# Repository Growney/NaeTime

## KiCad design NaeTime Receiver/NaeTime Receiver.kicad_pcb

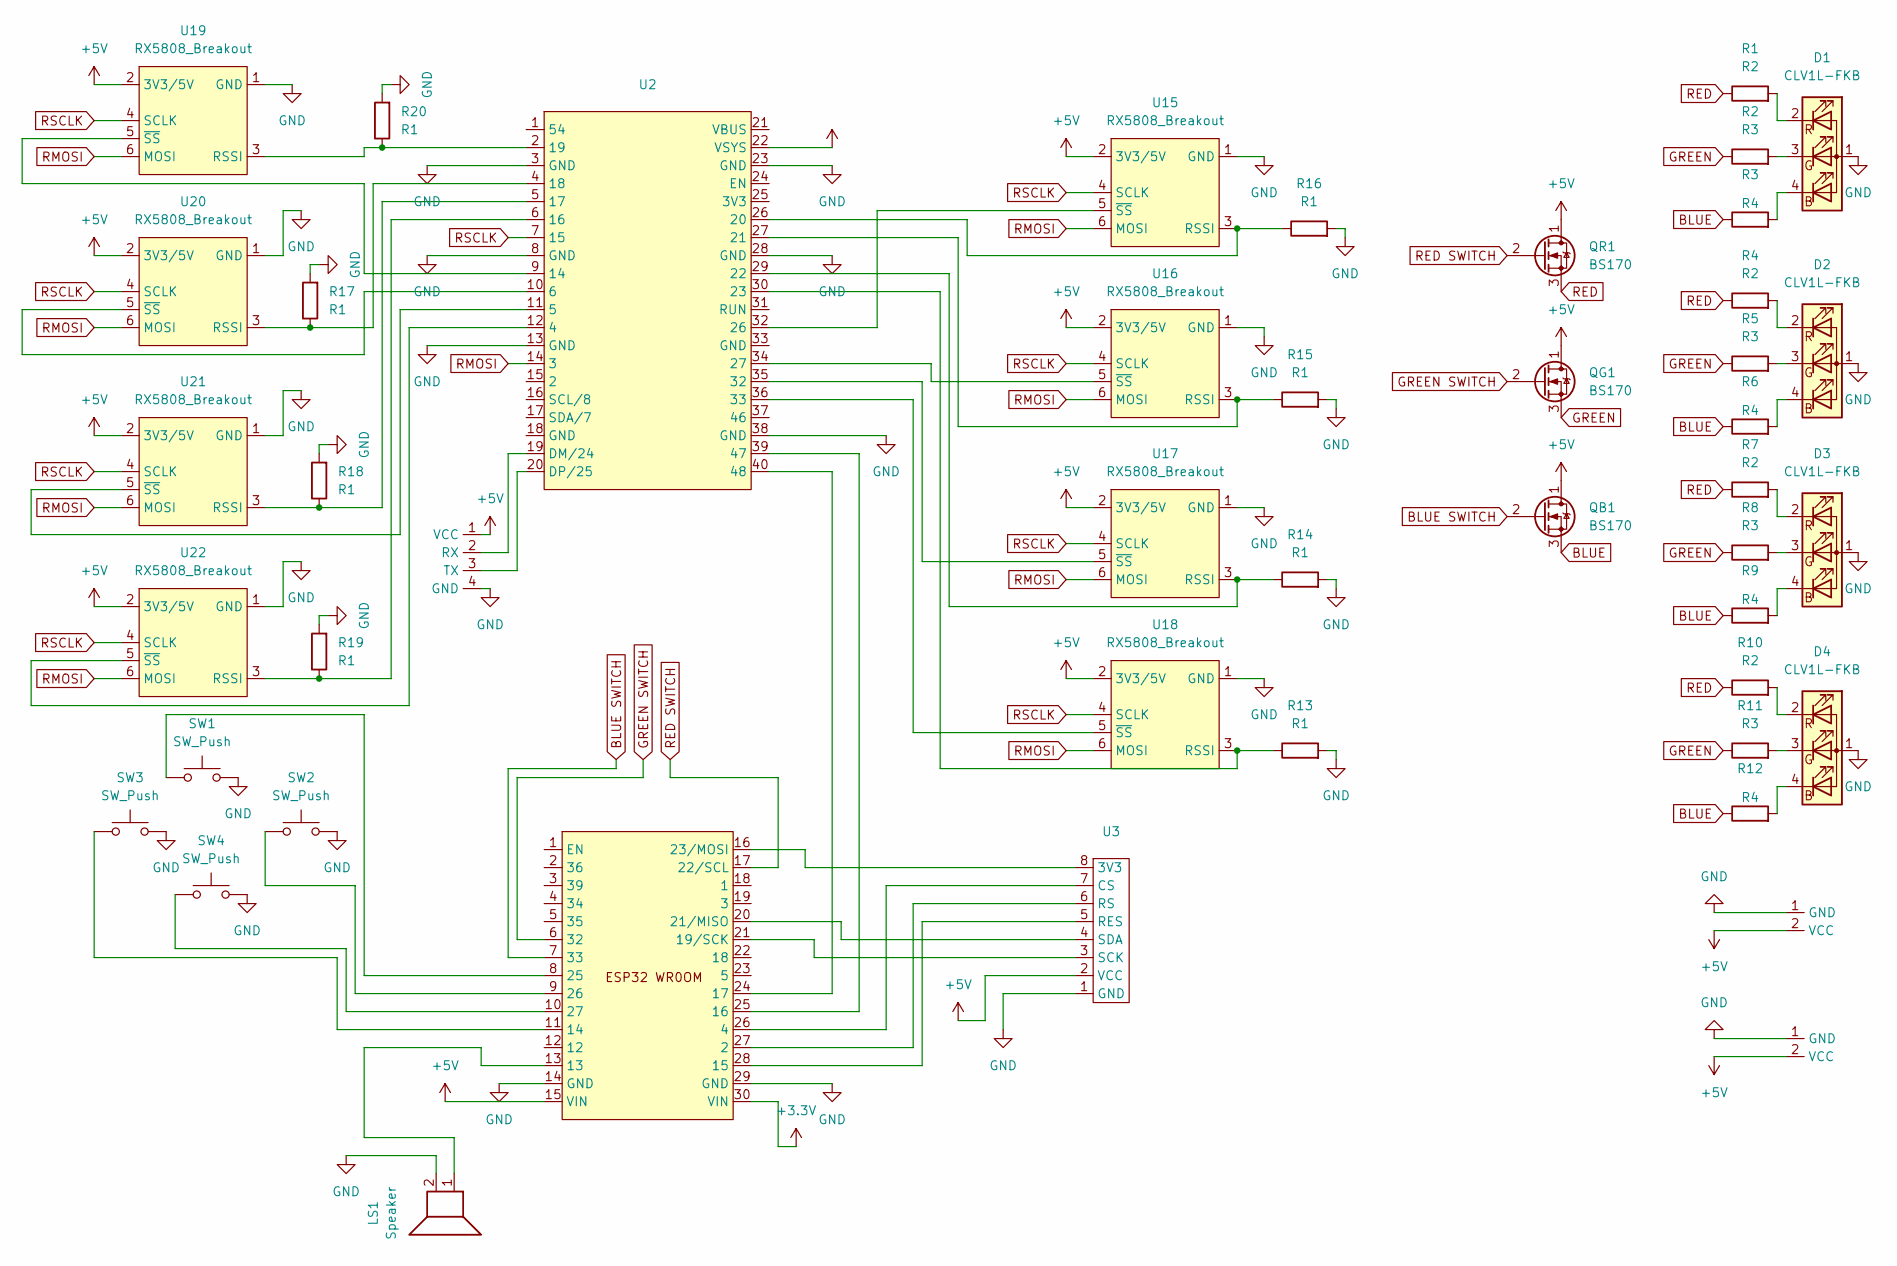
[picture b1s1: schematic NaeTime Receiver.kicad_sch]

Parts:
D1, D2, D3, D4: CLV1L-FKB; LED_D5.0mm-4_RGB GBCR
LS1: Speaker; Buzzer_12x9.5RM7.6
QB1: BS170; TO-92_Inline
QG1: BS170; TO-92_Inline
QR1: BS170; TO-92_Inline
R1, R4, R7, R10: R2; R_Axial_DIN0204_L3.6mm_D1.6mm_P7.62mm_Horizontal
R2, R5, R8, R11: R3; R_Axial_DIN0204_L3.6mm_D1.6mm_P7.62mm_Horizontal
R3, R6, R9, R12: R4; R_Axial_DIN0204_L3.6mm_D1.6mm_P7.62mm_Horizontal
R13, R14, R15, R16, R17, R18, R19, R20: R1; R_Axial_DIN0204_L3.6mm_D1.6mm_P7.62mm_Horizontal
SW1, SW2, SW3, SW4: SW_Push; SW_PUSH_6mm_H5mm
U1: ESP32 WROOM 30Pin Dev Board
U2: Wavestore ESP32-P4-ETH
U3: ST7735 Pin Header
U4: Exposed UART
U7, U8: Power Pads
U15, U16, U17, U18, U19, U20, U21, U22: RX5808_Breakout

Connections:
+3.3V: U1.30 (VIN)
+5V: QB1.1 (D), QG1.1 (D), QR1.1 (D), U1.15 (VIN), U2.22 (VSYS), U3.2 (VCC), U4.1 (VCC), U7.2 (VCC), U8.2 (VCC), U15.2 (3V3/5V), U16.2 (3V3/5V), U17.2 (3V3/5V), U18.2 (3V3/5V), U19.2 (3V3/5V), U20.2 (3V3/5V), U21.2 (3V3/5V), U22.2 (3V3/5V)
BLUE: QB1.3 (S), R3.1, R6.1, R9.1, R12.1
BLUE SWITCH: QB1.2 (G), U1.7 (33)
GND: D1.1 (A), D2.1 (A), D3.1 (A), D4.1 (A), LS1.2, R13.2, R14.2, R15.2, R16.2, R17.2, R18.2, R19.2, R20.2, SW1.2, SW2.2, SW3.2, SW4.2, U1.14 (GND), U1.29 (GND), U2.3 (GND), U2.8 (GND), U2.13 (GND), U2.23 (GND), U2.28 (GND), U2.38 (GND), U3.1 (GND), U4.4 (GND), U7.1 (GND), U8.1 (GND), U15.1 (GND), U16.1 (GND), U17.1 (GND), U18.1 (GND), U19.1 (GND), U20.1 (GND), U21.1 (GND), U22.1 (GND)
GREEN: QG1.3 (S), R2.1, R5.1, R8.1, R11.1
GREEN SWITCH: QG1.2 (G), U1.6 (32)
unnamed: D1.4 (BK), R3.2
unnamed: D1.3 (GK), R2.2
unnamed: D1.2 (RK), R1.2
unnamed: D2.4 (BK), R6.2
unnamed: D2.3 (GK), R5.2
unnamed: D2.2 (RK), R4.2
unnamed: D3.4 (BK), R9.2
unnamed: D3.3 (GK), R8.2
unnamed: D3.2 (RK), R7.2
unnamed: D4.4 (BK), R12.2
unnamed: D4.3 (GK), R11.2
unnamed: D4.2 (RK), R10.2
unnamed: LS1.1, U1.13
unnamed: U1.27 (2), U3.6 (RS)
unnamed: U1.26 (4), U3.7 (CS)
unnamed: SW3.1, U1.11 (14)
unnamed: U1.28 (15), U3.5 (RES)
unnamed: U1.25 (16), U2.39 (47)
unnamed: U1.24 (17), U2.40 (48)
unnamed: U1.21 (19/SCK), U3.3 (SCK)
unnamed: U1.20 (21/MISO), U3.4 (SDA)
unnamed: U1.16 (23/MOSI), U3.8 (3V3)
unnamed: SW1.1, U1.8 (25)
unnamed: SW2.1, U1.9 (26)
unnamed: SW4.1, U1.10 (27)
unnamed: U2.12 (4), U22.5 (~SS)
unnamed: U2.11 (5), U21.5 (~SS)
unnamed: U2.10 (6), U20.5 (~SS)
unnamed: R19.1, U2.6 (16), U22.3 (RSSI)
unnamed: R18.1, U2.5 (17), U21.3 (RSSI)
unnamed: R17.1, U2.4 (18), U20.3 (RSSI)
unnamed: U2.19 (DM/24), U4.2 (RX)
unnamed: U2.20 (DP/25), U4.3 (TX)
unnamed: R16.1, U2.26 (20), U15.3 (RSSI)
unnamed: U2.32 (26), U15.5 (~SS)
unnamed: R15.1, U2.27 (21), U16.3 (RSSI)
unnamed: U2.34 (27), U16.5 (~SS)
unnamed: R14.1, U2.29 (22), U17.3 (RSSI)
unnamed: U2.35 (32), U17.5 (~SS)
unnamed: R13.1, U2.30 (23), U18.3 (RSSI)
unnamed: U2.36 (33), U18.5 (~SS)
unnamed: R20.1, U2.2 (19), U19.3 (RSSI)
unnamed: U2.9 (14), U19.5 (~SS)
RED: QR1.3 (S), R1.1, R4.1, R7.1, R10.1
RED SWITCH: QR1.2 (G), U1.17 (22/SCL)
RMOSI: U2.14 (3), U15.6 (MOSI), U16.6 (MOSI), U17.6 (MOSI), U18.6 (MOSI), U19.6 (MOSI), U20.6 (MOSI), U21.6 (MOSI), U22.6 (MOSI)
RSCLK: U2.7 (15), U15.4 (SCLK), U16.4 (SCLK), U17.4 (SCLK), U18.4 (SCLK), U19.4 (SCLK), U20.4 (SCLK), U21.4 (SCLK), U22.4 (SCLK)

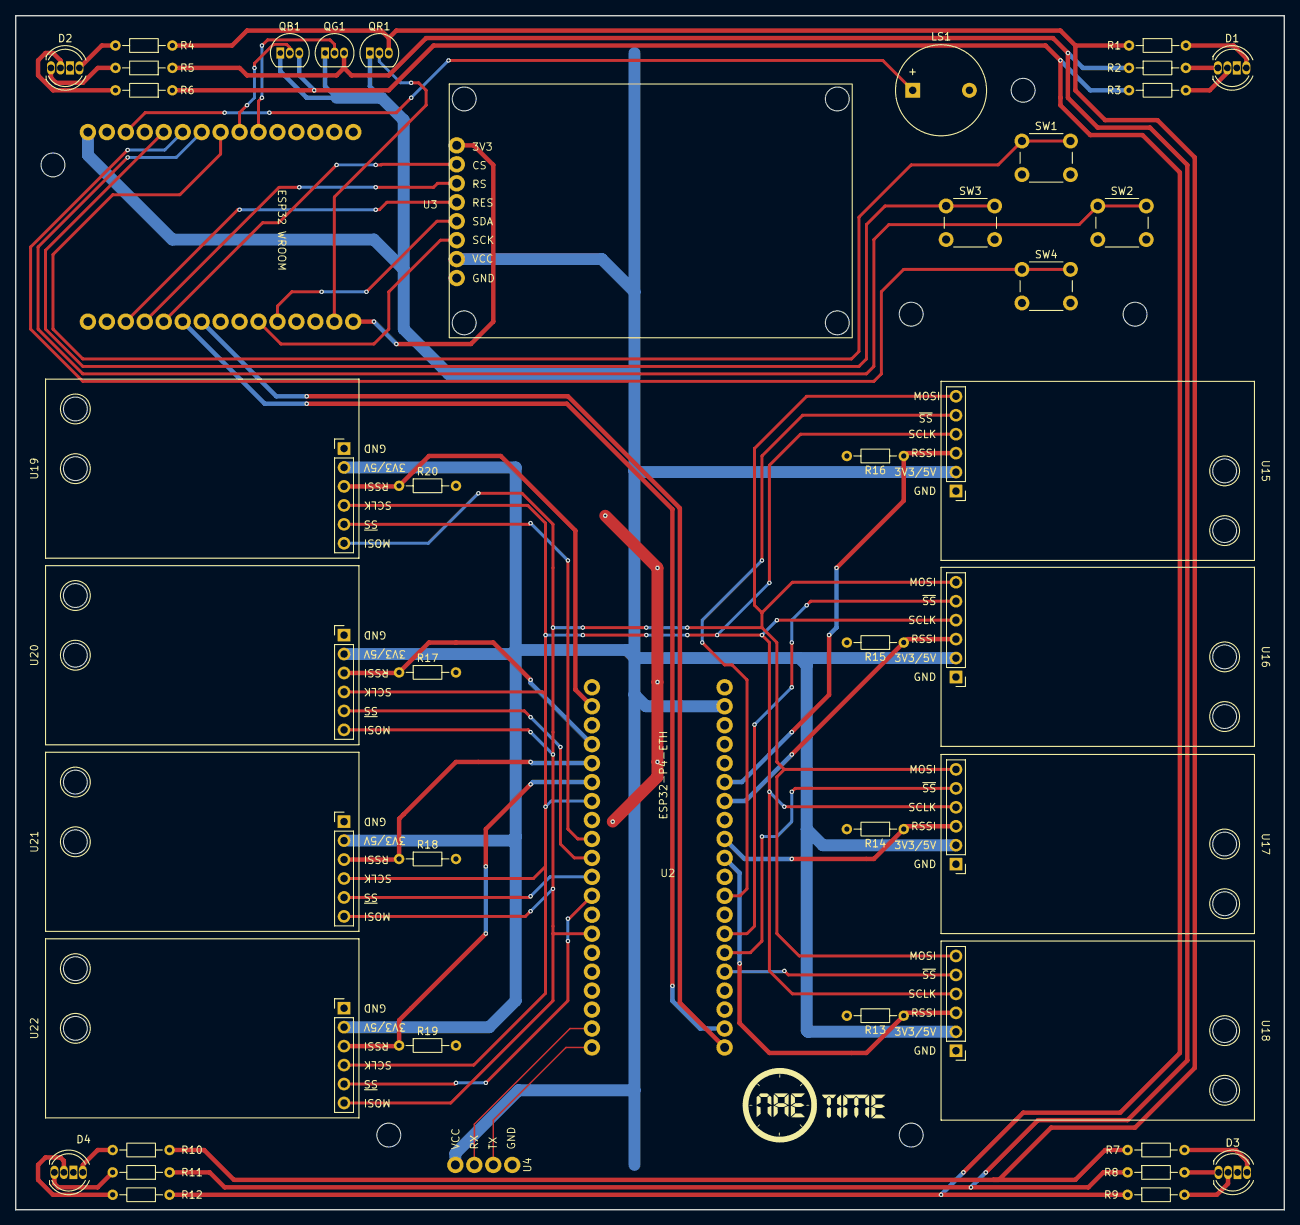
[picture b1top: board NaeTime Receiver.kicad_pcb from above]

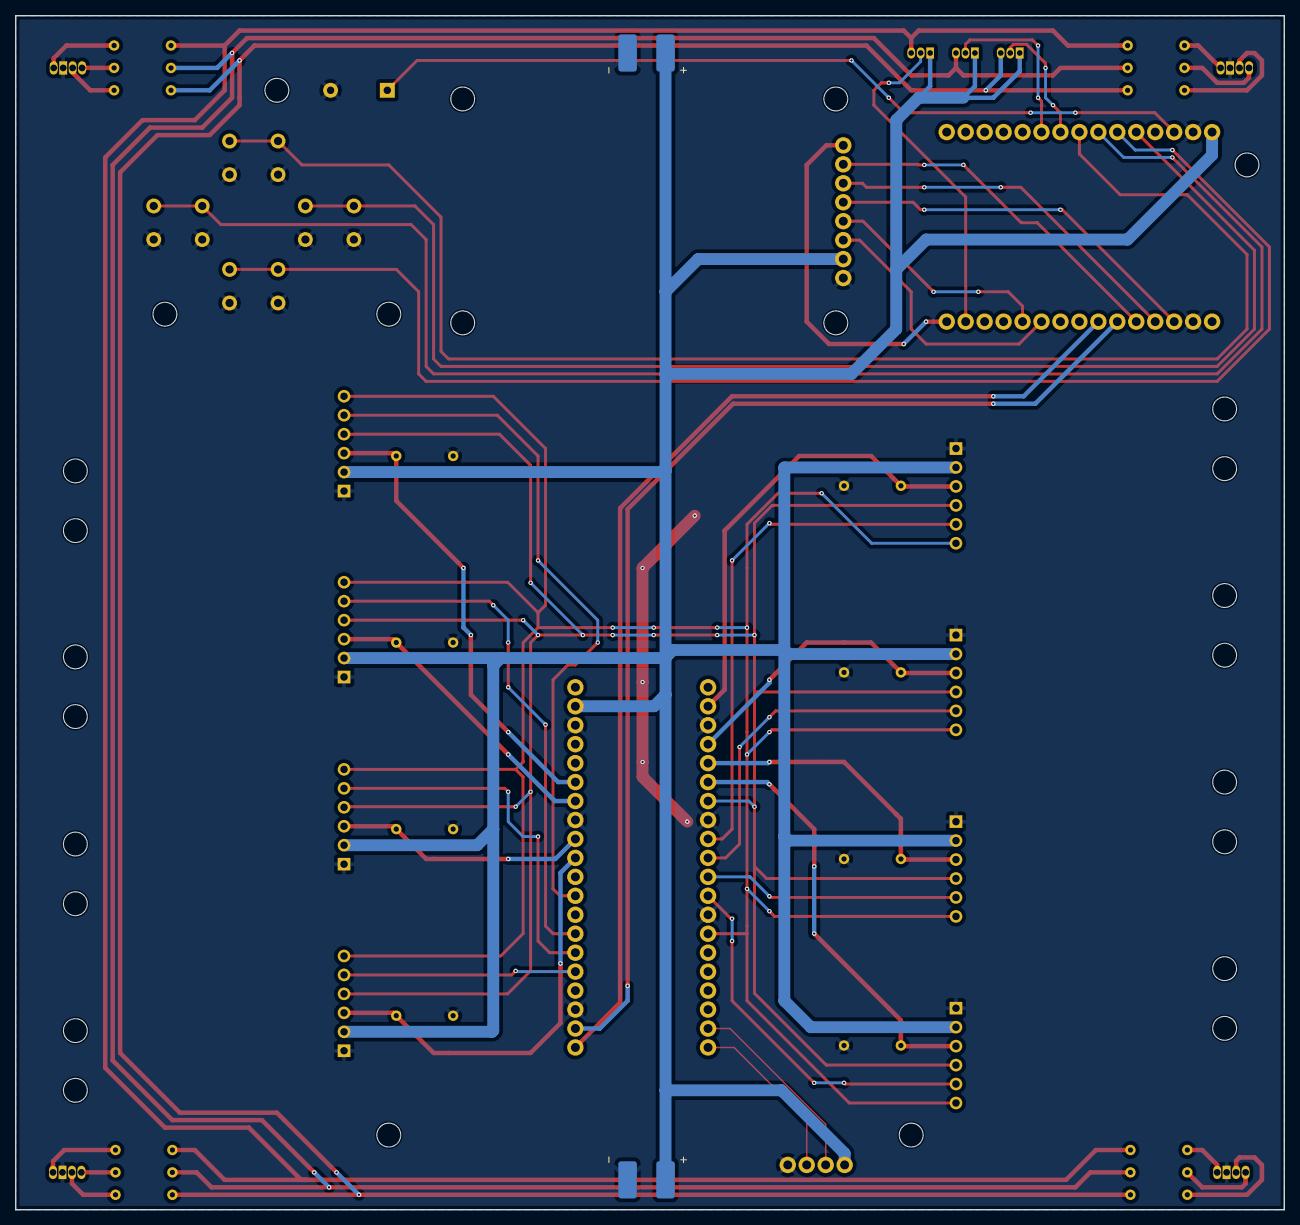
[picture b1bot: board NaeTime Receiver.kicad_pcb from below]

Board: 2 copper layers, 170.0 x 160.0 mm, 46 parts (2 on the bottom side), 53 nets.

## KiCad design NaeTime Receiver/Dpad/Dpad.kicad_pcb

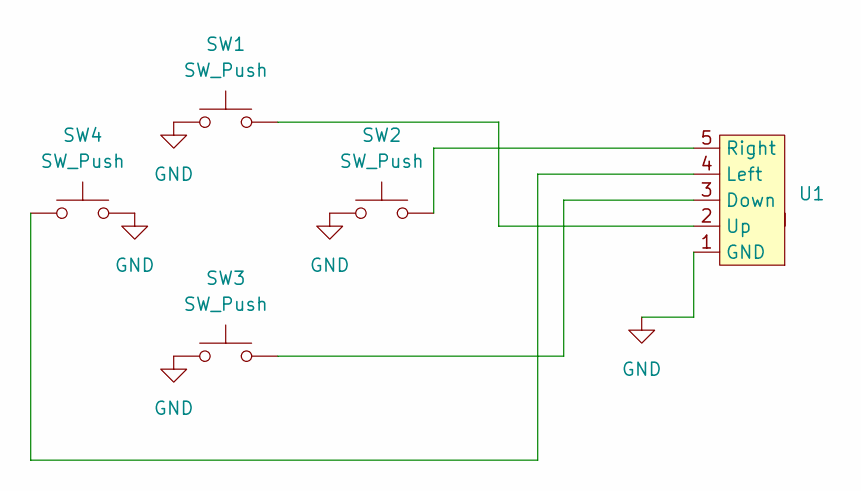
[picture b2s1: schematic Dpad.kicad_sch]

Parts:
SW1, SW2, SW3, SW4: SW_Push; SW_PUSH_6mm
U1: DPad Pin Header

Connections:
GND: SW1.1, SW2.1, SW3.1, SW4.2, U1.1 (GND)
unnamed: SW3.2, U1.3 (Down)
unnamed: SW4.1, U1.4 (Left)
unnamed: SW2.2, U1.5 (Right)
unnamed: SW1.2, U1.2 (Up)

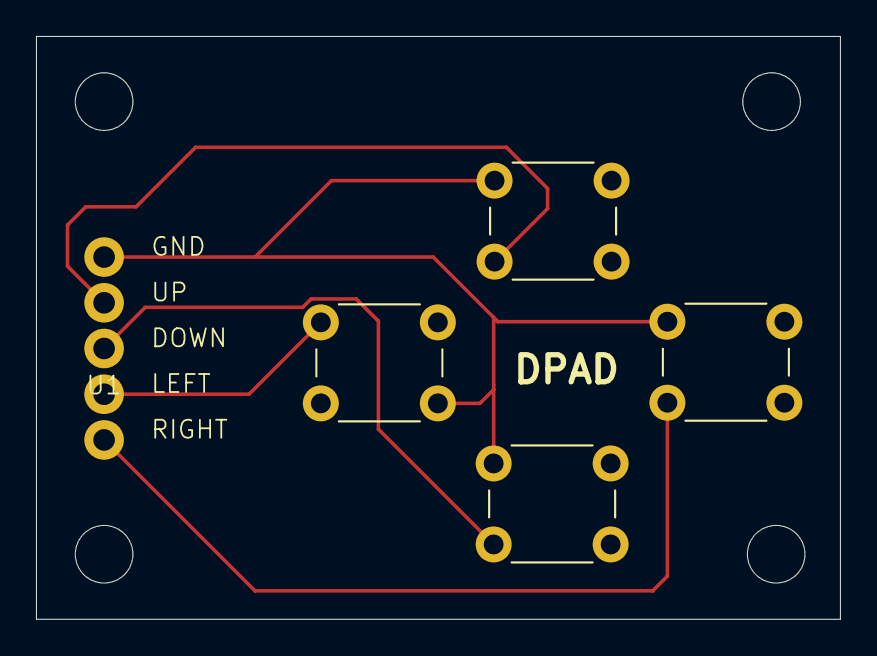
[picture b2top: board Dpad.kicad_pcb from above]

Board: 2 copper layers, 44.7 x 32.4 mm, 5 parts (0 on the bottom side), 5 nets.

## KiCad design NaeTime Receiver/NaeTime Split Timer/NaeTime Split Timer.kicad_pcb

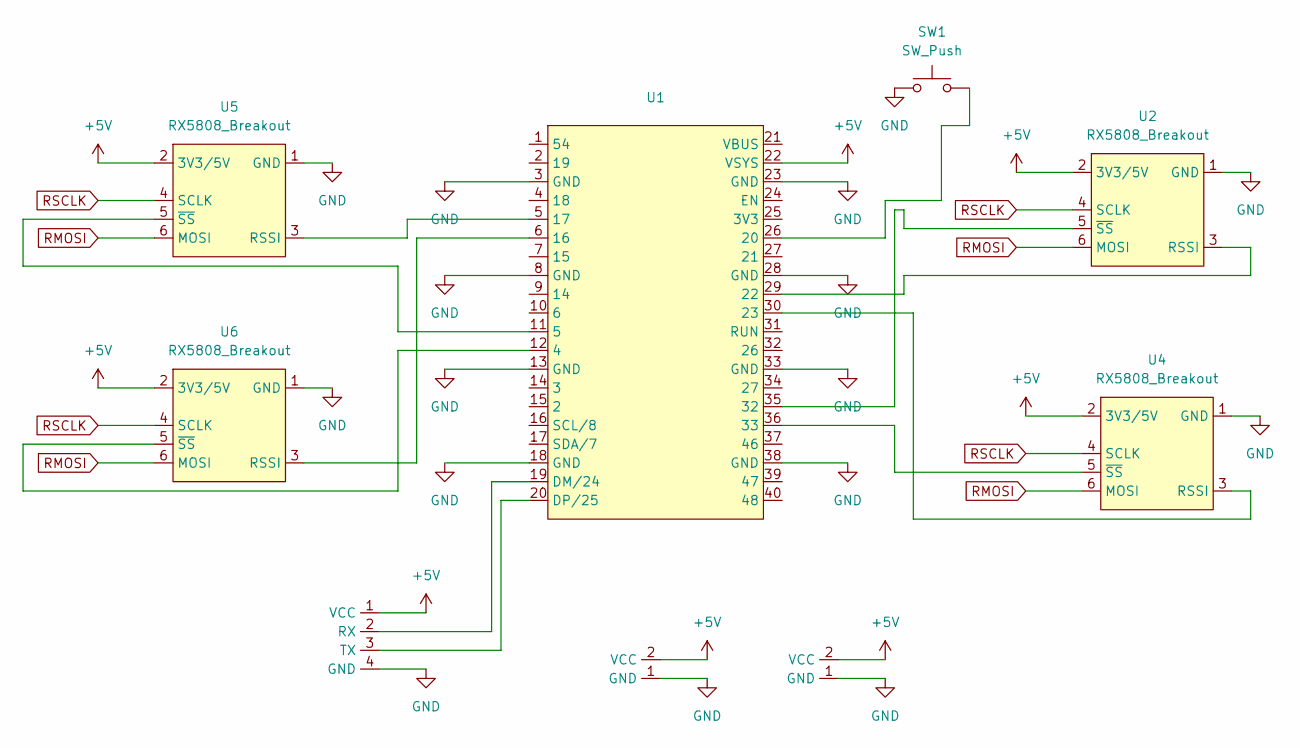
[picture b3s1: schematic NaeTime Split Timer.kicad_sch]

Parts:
SW1: SW_Push; SW_PUSH_6mm
U1: Wavestore ESP32-P4-ETH
U2, U4, U5, U6: RX5808_Breakout
U3: Exposed UART
U7, U8: Power Pads

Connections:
+5V: U1.22 (VSYS), U2.2 (3V3/5V), U3.1 (VCC), U4.2 (3V3/5V), U5.2 (3V3/5V), U6.2 (3V3/5V), U7.2 (VCC), U8.2 (VCC)
GND: SW1.1, U1.3 (GND), U1.8 (GND), U1.13 (GND), U1.18 (GND), U1.23 (GND), U1.28 (GND), U1.33 (GND), U1.38 (GND), U2.1 (GND), U3.4 (GND), U4.1 (GND), U5.1 (GND), U6.1 (GND), U7.1 (GND), U8.1 (GND)
unnamed: U1.12 (4), U6.5 (~SS)
unnamed: U1.11 (5), U5.5 (~SS)
unnamed: U1.6 (16), U6.3 (RSSI)
unnamed: U1.5 (17), U5.3 (RSSI)
unnamed: SW1.2, U1.26 (20)
unnamed: U1.29 (22), U2.3 (RSSI)
unnamed: U1.30 (23), U4.3 (RSSI)
unnamed: U1.35 (32), U2.5 (~SS)
unnamed: U1.36 (33), U4.5 (~SS)
unnamed: U1.19 (DM/24), U3.2 (RX)
unnamed: U1.20 (DP/25), U3.3 (TX)
RMOSI: U2.6 (MOSI), U4.6 (MOSI), U5.6 (MOSI), U6.6 (MOSI)
RSCLK: U2.4 (SCLK), U4.4 (SCLK), U5.4 (SCLK), U6.4 (SCLK)

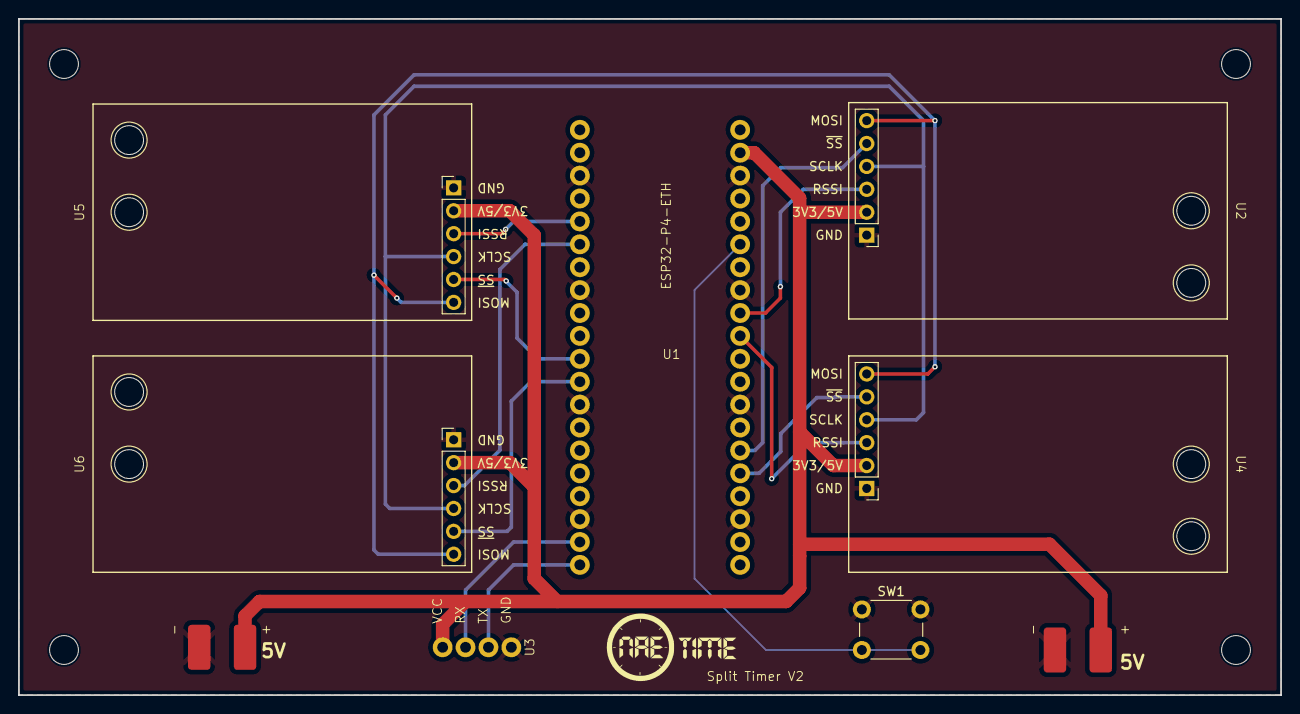
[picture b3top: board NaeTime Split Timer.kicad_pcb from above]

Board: 2 copper layers, 140.0 x 75.0 mm, 9 parts (0 on the bottom side), 15 nets.

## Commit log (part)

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2022-09-03 Initial
2023-03-01 Before Event store test
2023-04-26 initial event sourcing commit
2023-05-05 Tidy up classes
2023-12-08 Initial MAUI Client
2023-12-08 Initial client lib
2023-12-08 Hardware & Pilot local client implementation
2023-12-09 Configuration Page
2023-12-09 Enable and disable configuration
2023-12-09 Connection screen initial
2023-12-10 Connection page implementation
2023-12-11 Connect screen style
2023-12-11 Api configuration property component
2023-12-11 Return layout
2023-12-11 Proper with return layout
2023-12-11 Blank layout moved to layout instead of on the content page
2023-12-14 Before Projection refactor
2023-12-19 Update pilot
2023-12-21 LapRF8Channel update
2024-01-26 SQLite client
2024-01-26 Solution
2024-01-28 Pub sub
2024-01-28 timing
2024-01-28 Connection maintenance
2024-01-29 Pre Pub Sub
2024-01-29 Pub sub request response
2024-02-04 Before Nuke Lib
2024-02-05 Pub Sub Refactor
2024-02-06 Service Starts
2024-02-06 Get lap rf
2024-02-09 Practice Initial
2024-02-09 Split band and Frequency
2024-02-10 Rename configuration to lanes
2024-02-10 Remove pilot from lane configuration
2024-02-10 Timer disconnection
2024-02-10 Move lane elements to lane repo
2024-02-10 Timer lane syncing
2024-02-11 Fastest consecutive calculator
2024-02-11 Open Practice leaderboards initial
2024-02-11 Leaderboard efficiency
2024-02-12 Leaderboards
2024-02-14 Lap invalidation and themeing
2024-02-14 Consecutive leaderboards include the lap ids instead of start and end
2024-02-14 Remove Lap Number From Practice Laps and leaderboards
2024-02-14 Consecutive lap ordering
2024-02-16 Configure await false
2024-02-17 Lap Invalidation
2024-02-17 Button sizing and validate
2024-02-17 Recalculate leaderboards on lap re added
    rebase
2024-02-26 Partial leaderboard rewrite
2024-03-08 More leaderboard classes
2024-03-10 Far too many changes for a single commit
2024-03-10 Hot dam it builds nae chance it runs though
2024-03-10 Remove persistance projects from solution
2024-03-10 Add migrations
2024-03-11 Start database services first
    Leaderboards attempt
    Leaderboards
2024-03-12 Not really working consecutive leaderboards
    Consecutive Laps Leaderboard
2024-03-12 Single lap leaderboards
2024-03-12 Improved practice layout
2024-03-17 Total Lap Record Events
2024-03-17 Total Laps Storage Service
2024-03-17 Generic Leaderboard
2024-03-17 Total laps leaderboard manager
2024-03-17 Total laps leaderboard on practice
2024-05-05 List items
2024-05-12 PUB Sub changes
2024-05-12 Solution now building
2024-05-13 Handler fixes
2024-05-13 DI registrar scope
2024-05-13 Switch to explict types
2024-05-13 Add blank line after block
2024-05-20 Add sync fusion
2024-05-20 Threshold on the setup
    thresh
2024-05-20 Only get specific timers
2024-05-28 Timer connection announcements
2024-05-28 LapRF tunning and invalidate lap from leaderboard
2024-05-28 project reference for timer events
2024-05-31 Graphs and general improments
2024-05-31 Pilot Spark lines
2024-06-01 0.0.1.0 Publish
2024-06-28 Cut down announcements
2024-06-28 List items style
2024-06-28 String udp
2024-07-01 Rssi Filters
2024-07-03 Timer passes
2024-07-27 Tcp Comms
2024-07-28 Esp32 properties
2024-07-28 Announcement Grouping
2024-07-28 Remove replaced announcer classes
2024-07-28 Reimplement hardware announcements
2024-07-29 Standard deviation & consecutive lap display
2024-08-07 Lap count once
2024-08-07 Move PubSub to abstractions and InMemory
2024-09-28 Micro Python Node
2024-11-10 Micropython Node
2024-11-10 Fix packet event
2024-11-12 Sync word change
2025-01-19 Added hardware announcer service
2025-01-19 Micro python hardware updates
2025-01-25 Added node to timer app
2025-01-25 Node and receiver fixes
2025-02-02 Match receiver radio code with node
    Rssi Chart
2025-02-02 Node timing initial implementation
2025-02-03 Node timing fixes
2025-02-03 Enable disable node lanes
2025-02-11 Changed to six node device
2025-02-11 Added escape to ctrl c to stop device reboot
2025-03-04 Initial node commands
2025-03-04 Moved to single Database
2025-03-05 Initial timing deletion
2025-03-07 Added some events before going away
2025-03-23 Remove some warnings
2025-03-23 Remove RPC Invoke method
2025-03-23 Remove old persistence classes
2025-03-23 Move to dotnet 9
2025-03-23 UI RPC Removal
2025-03-24 Remove RPC (running)
2025-03-25 Move to syncfusion
2025-03-26 Initial move to orchestration
2025-03-30 Lane configuration moved to orchestrator
2025-03-30 Re initialise db migrations
2025-03-30 Resolved service creation loop
2025-03-30 Resolve orchestrator scope
2025-03-30 remove some style warnings
2025-03-30 Added start session events
2025-03-30 Remove style warnings
2025-03-30 Move orchestrator to scope
2025-03-30 Use created track id instead of creating own
2025-04-06 Resolve announcer ordering
2025-04-14 Hardware, management, openpractice orchestrators
2025-04-28 Very initial detection based laps
2025-05-08 Added ELRS backpack library
2025-05-12 backpack lap
2025-05-12 Command test app
2025-05-12 Added starting connection
2025-05-12 Minor changes to stop connection errors
2025-05-13 Working lap display
2025-06-13 Event db lite
2025-06-14 Reaction provider
2025-07-14 Who knows what i was doing, lets assume it was good
2025-08-02 Some aggregates and queries
2025-08-02 Added I query handler
2025-09-14 Command handlers
2025-09-14 Removed old references
2025-09-24 It builds, but at what cost
2025-09-27 Blazor web app client
2025-09-28 Open Practice session implementation start
2025-09-28 Sessions
2025-09-29 Session activation
2025-09-30 open practice screen initial
2025-09-30 Frequency Selection
2025-09-30 OG lane config control
2025-09-30 Pilot button group
2025-09-30 Open practice channels
2025-10-01 Reaction projection
2025-10-01 Timing events
2025-10-02 Live projection reactions
2025-10-02 Not working session detections
2025-10-03 Reactions
2025-10-03 String aggregate ids
2025-10-03 Generic aggregate IDs
2025-10-04 Pilot events
2025-10-05 Assigned detections
2025-10-06 Uhuh
2025-10-08 Some assignment bull
2025-10-14 before aggregate id class
2025-10-14 remove raise id
2025-10-14 before id aggregate root removal
2025-10-14 fixed messages and hings
2025-10-15 Before Move to Reaction Lap Events
2025-10-15 Not even building but time to watch traitors reaction timings
2025-10-16 Laps and stuff
2025-10-19 Open practice timing query
2025-10-19 Removed unused reaction stream variable name
2025-10-19 Added rough timing info to open practice screen
2025-10-19 Open Practice Timing events
2025-10-19 Remove db from git
2025-10-19 Remove open practice lap and timing events
2025-10-19 Update editor config
2025-10-19 Remove more db files from git
2025-10-19 Update git ignore
2025-10-19 Remove separate timing on sessions
2025-10-19 More ignoring db files
2025-10-19 Make pilot selection one button
2025-10-19 Live projections delay start up until they are caught up
2025-10-19 Add live projection services
2025-10-19 Move to any class is a projection
2025-10-19 Convert Open Practice timing to in memory live projection
2025-10-19 Move everything into memory
2025-10-19 Get last pilot detection
2025-10-19 Wait for projection version
    s
2025-10-20 Lap RF Hardware connection
2025-10-21 Detection refresh and timer status
2025-10-21 Rushed track minimum maximum
2025-10-21 Rushed text to speech
2025-10-25 Open practice lane component
2025-10-26 Lap RF configuration
2025-10-26 0 Based lane ids for lap RF (cause they should be)
2025-10-26 Lap RF connection events with issues
2025-10-26 Move laprf lane boundary to individual lanes
2025-10-26 Initial timer status implementation
2025-10-26 Timer statuses
2025-10-26 Mark as disconnected on app startup
2025-10-26 Danger disconnected icon
2025-10-26 Only trigger events when connected status changed
2025-10-26 Single status update
2025-10-27 Timer status update
2025-10-27 Lap groups
2025-10-27 Initial announcements
2025-10-29 Before reaction rethink
2025-10-30 Reaction rethink
2025-10-31 Lap announcements
2025-10-31 Announce channels
2025-10-31 Timer announcements
2025-10-31 Minimum lap warning text
2025-11-01 Initial overlay
2025-11-01 Basic overlay
2025-11-01 Configure await false on commands
2025-11-01 Render timer display on the client
2025-11-01 configure await false on append
2025-11-01 Remove entity framework core from connection
2025-11-05 LapRF tuning
2025-11-10 Dispose of reactions
2025-11-11 Only announce single and 3 lap records
2025-11-11 Remove unused Reaction handler factory
2025-11-11 Read back new global id on save
2025-11-11 Dirty AF single writes
2025-11-12 DB write singles
2025-11-12 catch cancellation exception
2025-11-17 only announce single laps
2025-11-17 Timing moments
2025-11-22 Detection validation
2025-11-22 Only show timing on active sessions
2025-11-22 Show assigned pilots on config list not all
2025-11-22 Mud blazor theme tables
2025-11-22 Theme create buttons
2025-11-22 Theme create pilot
2025-11-22 Theme create lap rf
2025-11-22 Theme create session
2025-11-22 Theme create track
2025-11-22 Theme edit ethernet lap rf
2025-11-22 Theme edit pilot
2025-11-22 Theme edit track
2025-11-23 Broken style
2025-11-23 Slightly better but in need of scroll
2025-11-24 grid based timeline
2025-11-24 Horizontal scrolling timeline
2025-11-25 Custom grids and flex boxes
2025-11-25 Audio / text announcers
2025-11-25 Marshal / results ui
2025-11-27 increase the size of marshalling
2025-11-27 Sort standard deviation correctly
2025-11-27 Invalidate detections before detection
2025-11-27 Reduce column header text for consecutive
2025-11-27 Top 10 Std deviation
2025-11-27 Increase results table font size
2025-12-02 Remove milliseconds from timer to increase performance
2025-12-02 Invalidate until add end of pack
2025-12-02 Clone sessions
2025-12-03 Move reactions to own project
2025-12-05 Phase 1 API
2025-12-05 Clients and not working client
2025-12-05 Not working conversion to client side
2025-12-06 Partially working wasm events
2025-12-07 Revert "Remove milliseconds from timer to increase performance"
    This reverts commit 72aee0991829bcfd9ac1a8a569be9023068b312c.
2025-12-07 Bogged down single signal R connection
2025-12-07 only update last detection if its the same pilot
2025-12-07 Use periodic timer
2025-12-07 Removed event logging
2025-12-07 Request logging to info
2025-12-07 Events async
2025-12-07 Update to dotnet 10
2025-12-07 Multi-threading
2025-12-07 Disable aspnet logging
2025-12-07 remove milliseconds again
2025-12-07 Added reaction logging
2025-12-08 Detection events
2025-12-08 Min max lap time on session instead of track
2025-12-13 Micropython test
2025-12-16 Store RSSI in the event stream to allow for easy tuning
2026-01-17 ESP Node
2026-01-17 Nae Time Node
2026-01-19 Naetime node comms
2026-01-19 Start connection after its added to the provider
2026-01-19 Initialise on connect
2026-01-19 always log connected or disconnected events to confirm configuration
2026-01-20 Basic RSSI Optimization (No Storage)
2026-01-20 Server speech
2026-01-21 Extra init stuff on node
2026-01-25 Partial move rssi out of the rssi chart
2026-01-27 64bit time
2026-02-05 Receiver pcb
2026-02-05 Nae Races solution
2026-02-05 Sqlite Abstraction
2026-02-05 Untested kurrentdb
2026-03-08 Fab and node menu
2026-04-24 general fixes
2026-05-04 Move to submodule
2026-05-05 Move to class positions
2026-05-09 Open practice snapshotting
2026-05-11 Better backpack interface stability
